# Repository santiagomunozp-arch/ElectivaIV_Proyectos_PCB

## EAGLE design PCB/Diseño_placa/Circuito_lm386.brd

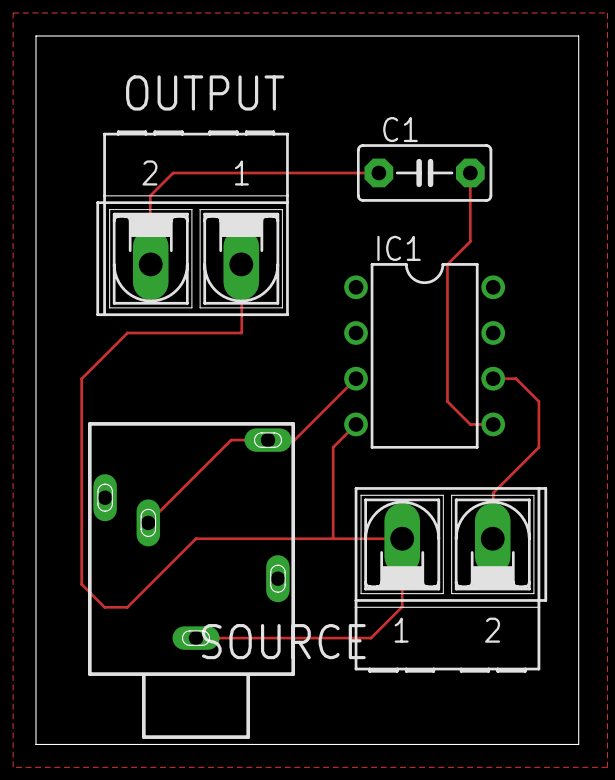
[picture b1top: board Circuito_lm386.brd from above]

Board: 2 copper layers, 30.2 x 39.4 mm, 5 parts (0 on the bottom side), 5 nets.

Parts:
C1: 220 uF; C5B3
IC1: LM386N-1; DIL08
OUTPUT: AK500/2-H
SOURCE: AK500/2-H
X3: 1503_09

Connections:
unnamed: IC1.3, X3.4, X3.5
unnamed: IC1.6, SOURCE.2
unnamed: IC1.4, OUTPUT.1, SOURCE.1, X3.1
unnamed: C1.2, IC1.5
unnamed: C1.1, OUTPUT.2
